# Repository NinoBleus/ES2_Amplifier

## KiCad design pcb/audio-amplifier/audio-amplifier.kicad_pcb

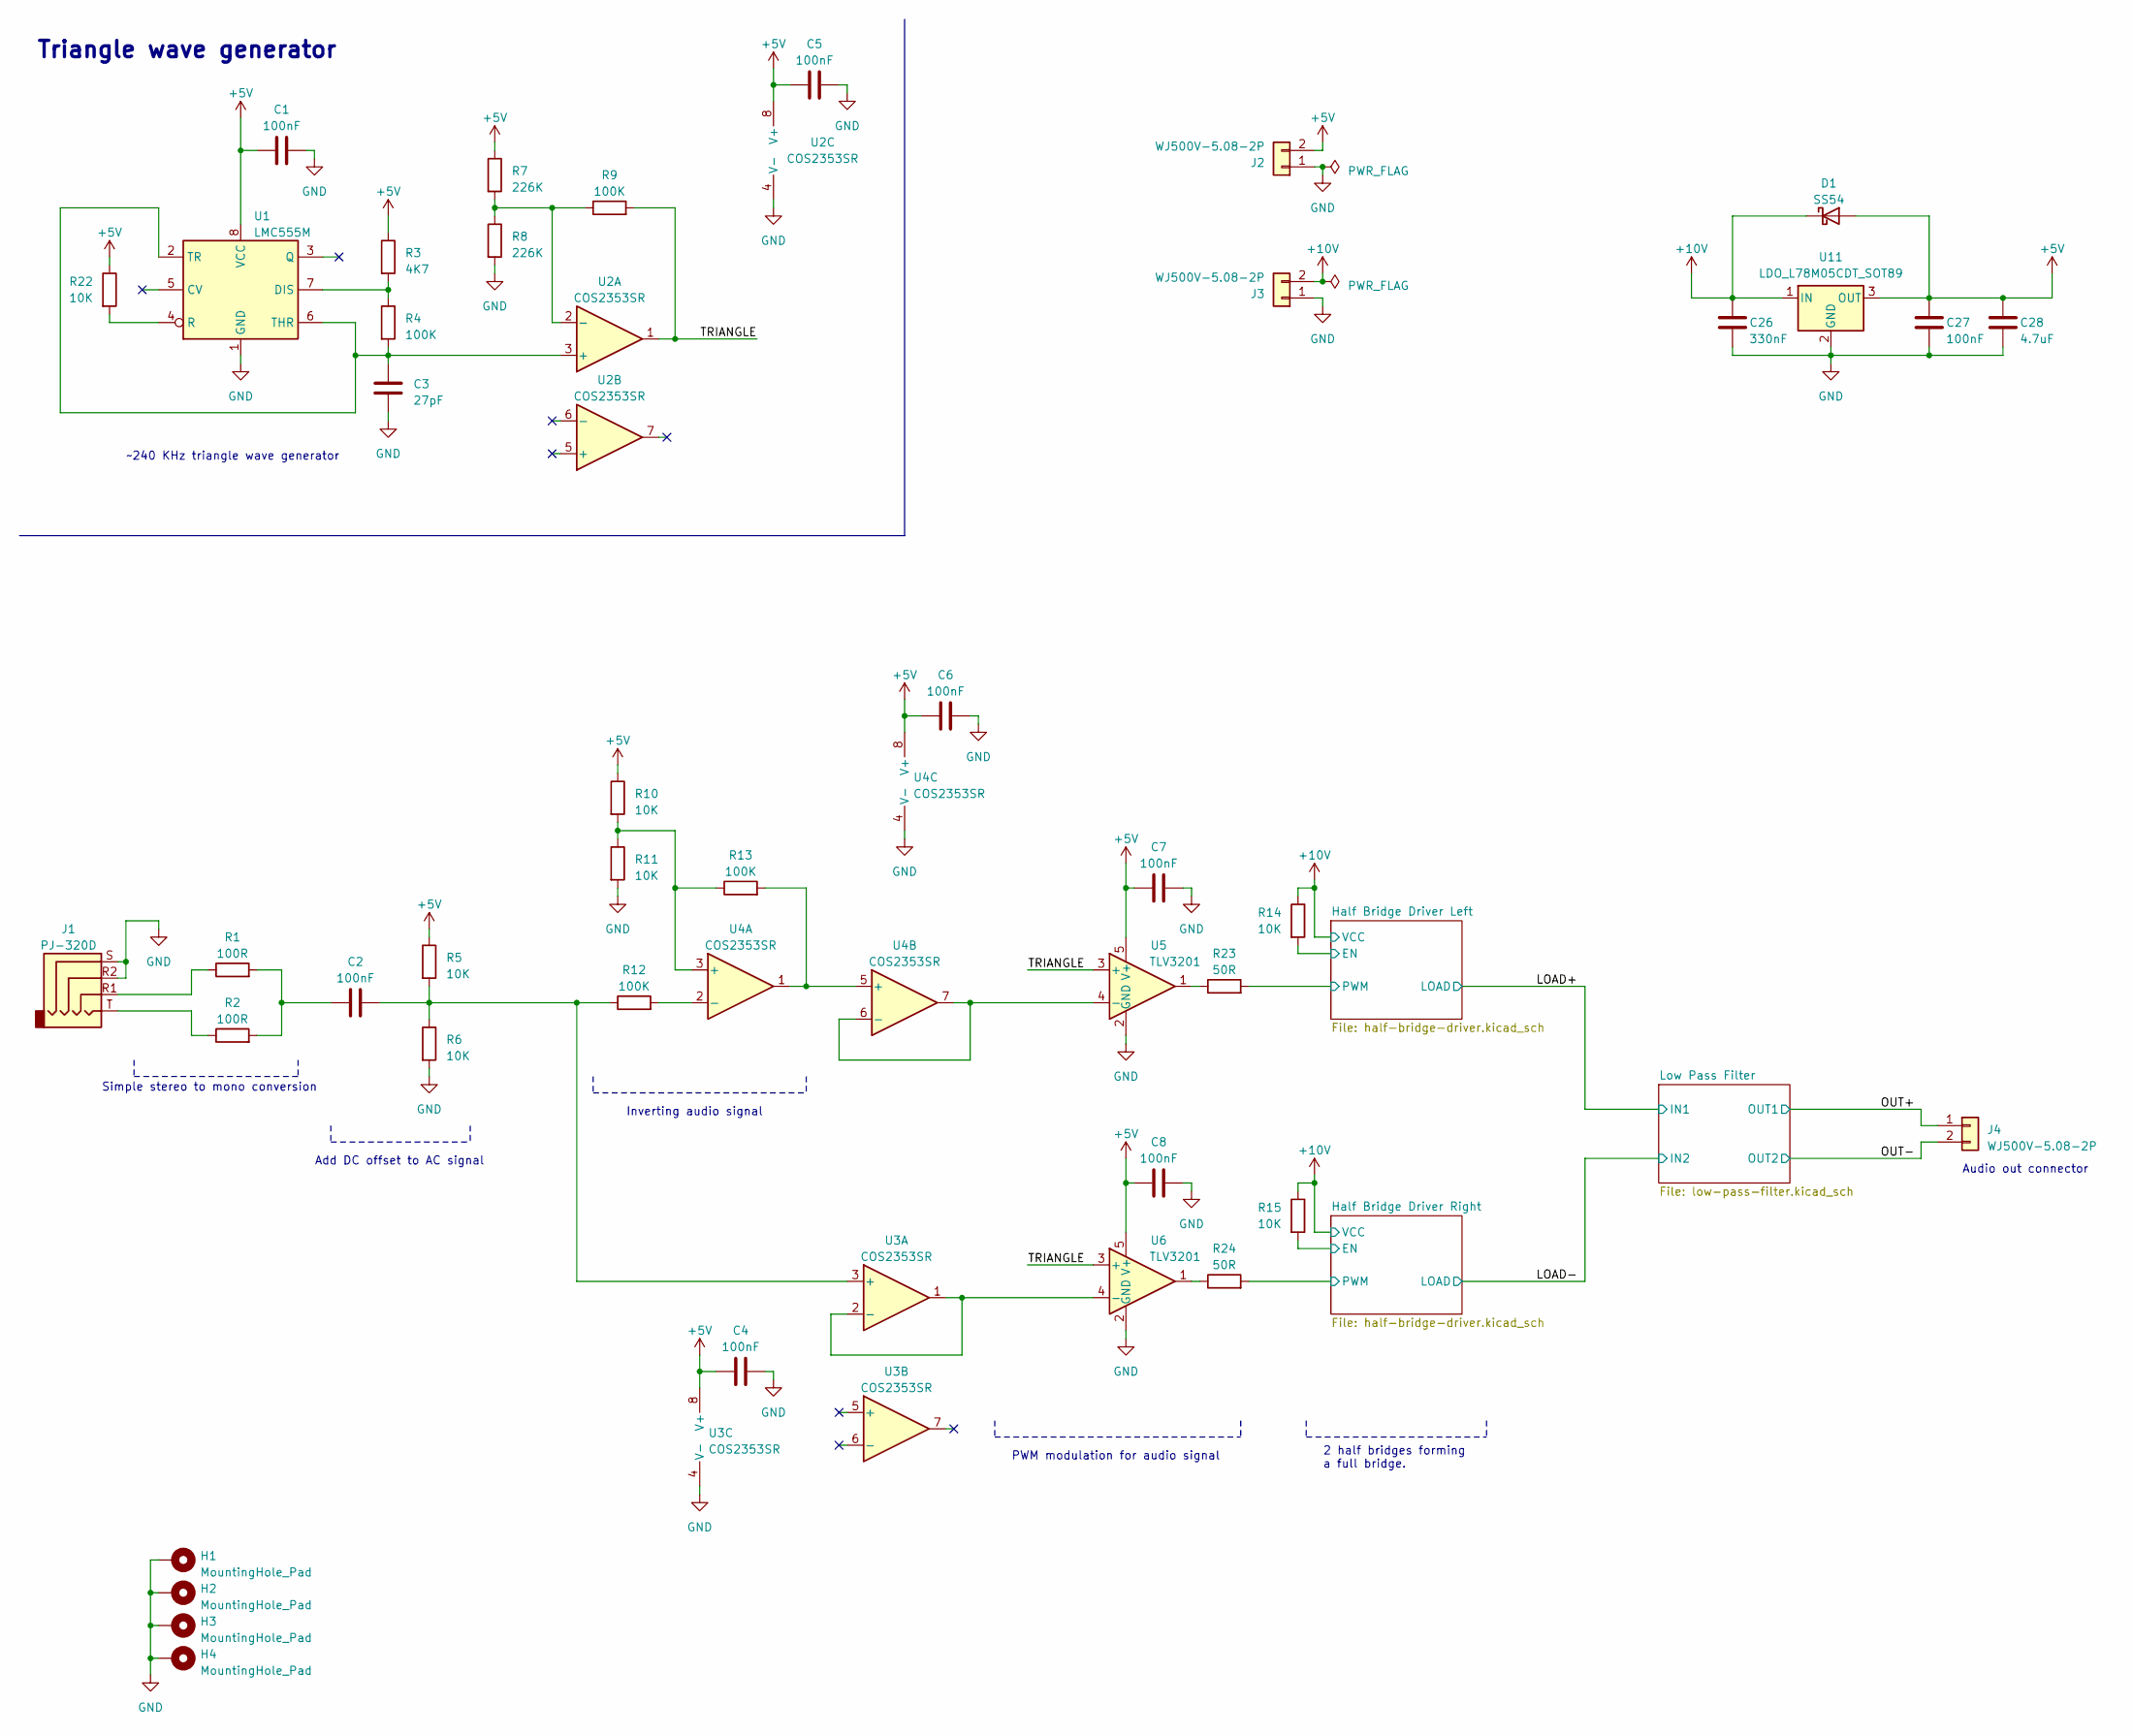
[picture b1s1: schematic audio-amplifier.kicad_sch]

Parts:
C1, C2, C4, C5, C6, C7, C8, C27: 100nF; C_0805_2012Metric; MPN CC0805KRX7R9BB104; LCSC Part # C49678
C3: 27pF; C_0603_1608Metric; MPN GRM1885C1H270FA01D; LCSC Part # C162215
C26: 330nF; C_0805_2012Metric; MPN 0805B334K500NT; LCSC Part # C1740
C28: 4.7uF; C_1206_3216Metric; MPN 1206B475K500NT; LCSC Part # C29823
D1: SS54; D_SMA_Handsoldering; MPN SS54; LCSC Part # C22452
H1, H2, H3, H4: MountingHole_Pad; MountingHole_3.2mm_M3_Pad_Via
J1: PJ-320D; Jack_3.5mm_PJ320D_Horizontal; LCSC Part # C431535
J2, J3, J4: WJ500V-5.08-2P; TerminalBlock_bornier-2_P5.08mm; MPN WJ500V-5.08-2P; LCSC Part # C8465
R1, R2: 100R; R_0805_2012Metric; LCSC Part # C17408
R3: 4K7; R_0603_1608Metric; MPN ARG03BTC4701; LCSC Part # C309085
R4: 100K; R_0603_1608Metric; MPN ARG03BTC1003; LCSC Part # C335088
R5, R6, R10, R11, R14, R15, R22: 10K; R_0805_2012Metric; MPN 0805W8F1002T5E; LCSC Part # C17414
R7, R8: 226K; R_0805_2012Metric; MPN RT0805BRD07226KL; LCSC Part # C865308
R9, R12, R13: 100K; R_0805_2012Metric; MPN 0805W8F1003T5E; LCSC Part # C149504
R23, R24: 50R; R_0805_2012Metric; MPN ARG05FTC0500; LCSC Part # C2828866
U1: LMC555M; SOP-8_3.9x4.9mm_P1.27mm; LCSC Part # C356725
U2, U3, U4: COS2353SR; SOP-8_3.9x4.9mm_P1.27mm; LCSC Part # C2685365
U5, U6: TLV3201; SOT-23-5; LCSC Part # C105188
U11: LDO_L78M05CDT_SOT89; TO-252-2; MPN L78M05CDT; LCSC Part # C55509

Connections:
+5V: C1.1, C4.1, C5.1, C6.1, C7.1, C8.1, C27.1, C28.1, D1.2 (A), J2.2, R3.1, R5.1, R7.1, R10.1, R22.1, U1.8 (VCC), U2.8 (V+), U3.8 (V+), U4.8 (V+), U5.5 (V+), U6.5 (V+), U11.3 (OUT); also elsewhere on the board
+10V: C26.1, D1.1 (K), J3.2, R14.1, R15.1, U11.1 (IN); also elsewhere on the board
/Half Bridge Driver Left/EN: R14.2; also elsewhere on the board
/Half Bridge Driver Left/PWM: R23.2; also elsewhere on the board
/Half Bridge Driver Right/EN: R15.2; also elsewhere on the board
/Half Bridge Driver Right/PWM: R24.2; also elsewhere on the board
/OUT+: J4.1; also elsewhere on the board
/OUT-: J4.2; also elsewhere on the board
/TRIANGLE: R9.2, U2.1, U5.3 (+), U6.3 (+)
GND: C1.2, C3.2, C4.2, C5.2, C6.2, C7.2, C8.2, C26.2, C27.2, C28.2, H1.1, H2.1, H3.1, H4.1, J1.R2, J1.S, J2.1, J3.1, R6.2, R8.2, R11.2, U1.1 (GND), U2.4 (V-), U3.4 (V-), U4.4 (V-), U5.2 (GND), U6.2 (GND), U11.2 (GND); also elsewhere on the board
unnamed: C2.1, R1.2, R2.2
unnamed: J1.R1, R1.1
unnamed: J1.T, R2.1
unnamed: R23.1, U5.1
unnamed: R24.1, U6.1
unnamed: R3.2, R4.1, U1.7 (DIS)
unnamed: R22.2, U1.4 (R)
unnamed: C3.1, R4.2, U1.2 (TR), U1.6 (THR), U2.3 (+)
unnamed: R7.2, R8.1, R9.1, U2.2 (-)
unnamed: C2.2, R5.2, R6.1, R12.1, U3.3 (+)
unnamed: U3.1, U3.2 (-), U6.4 (-)
unnamed: R10.2, R11.1, R13.1, U4.3 (+)
unnamed: R12.2, U4.2 (-)
unnamed: R13.2, U4.1, U4.5 (+)
unnamed: U4.6 (-), U4.7, U5.4 (-)

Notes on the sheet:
Audio out connector
Simple stereo to mono conversion
PWM modulation for audio signal
~240 KHz triangle wave generator
Inverting audio signal
Add DC offset to AC signal
2 half bridges forming a full bridge.
Triangle wave generator

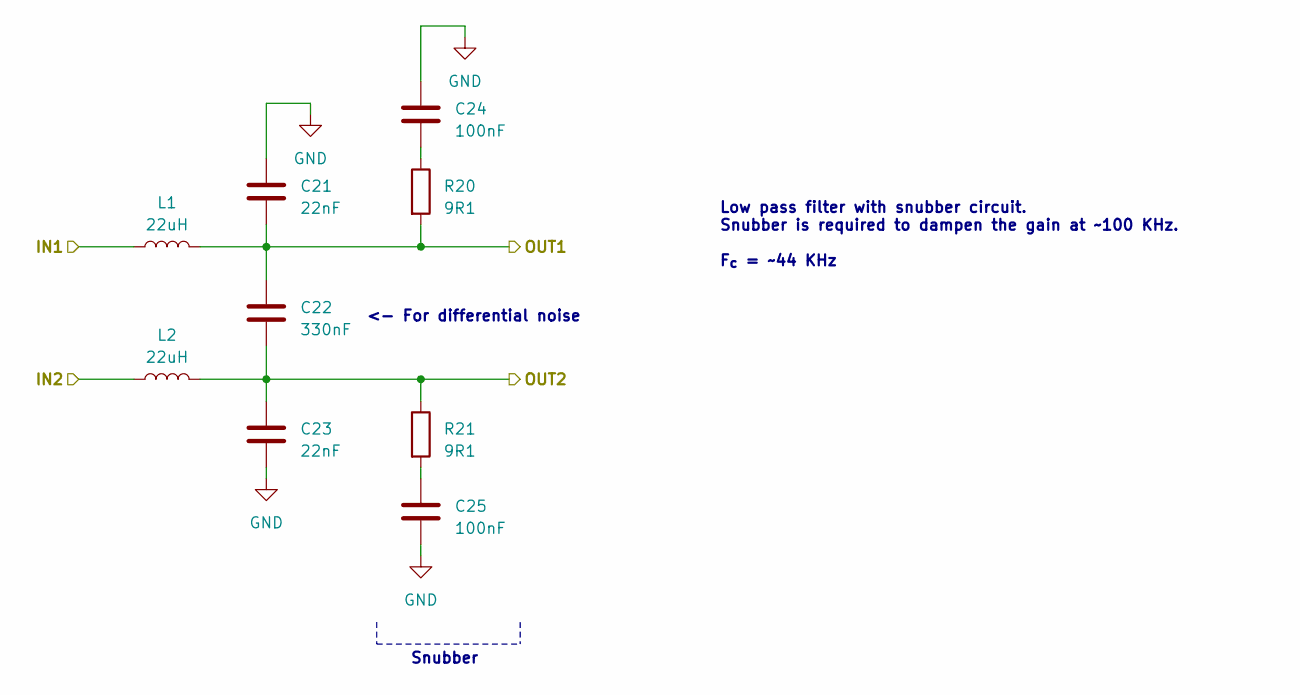
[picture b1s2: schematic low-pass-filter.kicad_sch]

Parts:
C21, C23: 22nF; C_0805_2012Metric; MPN CL21B223KBANNNC; LCSC Part # C1729
C22: 330nF; C_0805_2012Metric; MPN 0805B334K500NT; LCSC Part # C1740
C24, C25: 100nF; C_0805_2012Metric; MPN CC0805KRX7R9BB104; LCSC Part # C49678
L1, L2: 22uH; L_Sunlord_SWPA6045S; MPN SWPA6045S220MT; LCSC Part # C83454
R20, R21: 9R1; R_0805_2012Metric; MPN FRC0805F9R10TS; LCSC Part # C2933515

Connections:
/LOAD+: L1.1; also elsewhere on the board
/LOAD-: L2.1; also elsewhere on the board
/OUT+: C21.2, C22.1, L1.2, R20.2; also elsewhere on the board
/OUT-: C22.2, C23.1, L2.2, R21.1; also elsewhere on the board
GND: C21.1, C23.2, C24.1, C25.2; also elsewhere on the board
unnamed: C24.2, R20.1
unnamed: C25.1, R21.2

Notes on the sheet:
<- For differential noise
Low pass filter with snubber circuit. Snubber is required to dampen the gain at ~100 KHz. F_{c} = ~44 KHz
Snubber

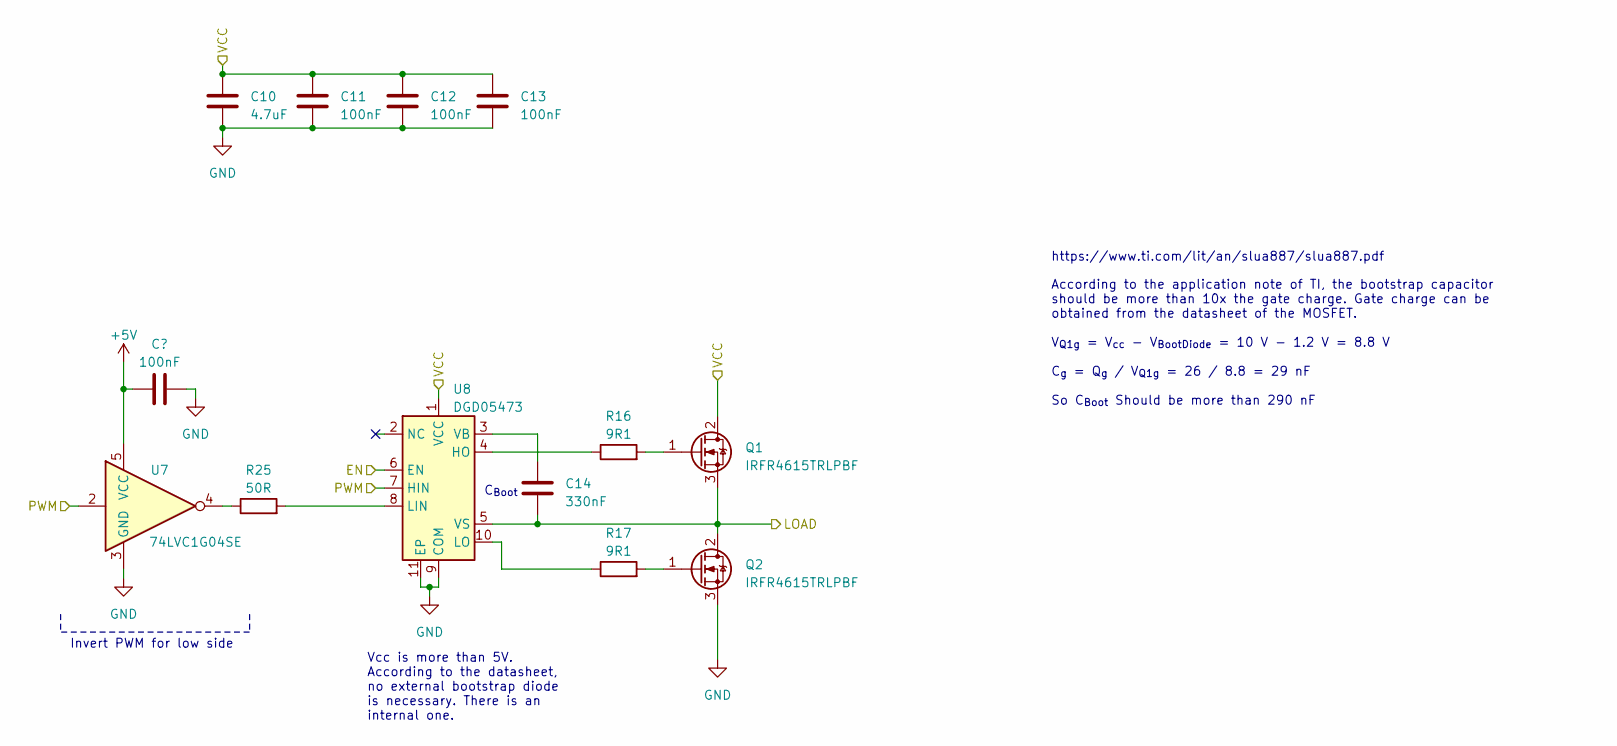
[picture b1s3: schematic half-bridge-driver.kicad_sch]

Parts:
C9, C11, C12, C13: 100nF; C_0805_2012Metric; MPN CC0805KRX7R9BB104; LCSC Part # C49678
C10: 4.7uF; C_1206_3216Metric; MPN 1206B475K500NT; LCSC Part # C29823
C14: 330nF; C_0805_2012Metric; MPN 0805B334K500NT; LCSC Part # C1740
Q1, Q2: IRFR4615TRLPBF; TO-252-2; MPN IRFR4615TRLPBF; LCSC Part # C148159
R16, R17: 9R1; R_0805_2012Metric; MPN FRC0805F9R10TS; LCSC Part # C2933515
R25: 50R; R_0805_2012Metric; MPN ARG05FTC0500; LCSC Part # C2828866
U7: 74LVC1G04SE; SOT-353_SC-70-5; MPN 74LVC1G04SE; LCSC Part # C264081
U8: DGD05473; DFN-10-1EP_3x3mm_P0.5mm_EP1.65x2.38mm; LCSC Part # C189752

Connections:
+5V: C9.1, U7.5 (VCC); also elsewhere on the board
+10V: C10.1, C11.1, C12.1, C13.1, Q1.2 (D), U8.1 (VCC); also elsewhere on the board
/Half Bridge Driver Left/EN: U8.6 (EN); also elsewhere on the board
/Half Bridge Driver Left/PWM: U7.2, U8.7 (HIN); also elsewhere on the board
/LOAD+: C14.2, Q1.3 (S), Q2.2 (D), U8.5 (VS); also elsewhere on the board
GND: C9.2, C10.2, C11.2, C12.2, C13.2, Q2.3 (S), U7.3 (GND), U8.9 (COM), U8.11 (EP); also elsewhere on the board
unnamed: Q1.1 (G), R16.2
unnamed: Q2.1 (G), R17.2
unnamed: R25.1, U7.4
unnamed: R16.1, U8.4 (HO)
unnamed: R25.2, U8.8 (LIN)
unnamed: R17.1, U8.10 (LO)
unnamed: C14.1, U8.3 (VB)

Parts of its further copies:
C15, C17, C18, C19: 100nF; C_0805_2012Metric; MPN CC0805KRX7R9BB104; LCSC Part # C49678
C16: 4.7uF; C_1206_3216Metric; MPN 1206B475K500NT; LCSC Part # C29823
C20: 330nF; C_0805_2012Metric; MPN 0805B334K500NT; LCSC Part # C1740
Q3, Q4: IRFR4615TRLPBF; TO-252-2; MPN IRFR4615TRLPBF; LCSC Part # C148159
R18, R19: 9R1; R_0805_2012Metric; MPN FRC0805F9R10TS; LCSC Part # C2933515
R26: 50R; R_0805_2012Metric; MPN ARG05FTC0500; LCSC Part # C2828866
U9: 74LVC1G04SE; SOT-353_SC-70-5; MPN 74LVC1G04SE; LCSC Part # C264081
U10: DGD05473; DFN-10-1EP_3x3mm_P0.5mm_EP1.65x2.38mm; LCSC Part # C189752

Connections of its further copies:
+5V: C15.1, U9.5 (VCC); also elsewhere on the board
+10V: C16.1, C17.1, C18.1, C19.1, Q3.2 (D), U10.1 (VCC); also elsewhere on the board
/Half Bridge Driver Right/EN: U10.6 (EN); also elsewhere on the board
/Half Bridge Driver Right/PWM: U9.2, U10.7 (HIN); also elsewhere on the board
/LOAD-: C20.2, Q3.3 (S), Q4.2 (D), U10.5 (VS); also elsewhere on the board
GND: C15.2, C16.2, C17.2, C18.2, C19.2, Q4.3 (S), U9.3 (GND), U10.9 (COM), U10.11 (EP); also elsewhere on the board
unnamed: Q3.1 (G), R18.2
unnamed: Q4.1 (G), R19.2
unnamed: R26.1, U9.4
unnamed: R18.1, U10.4 (HO)
unnamed: R26.2, U10.8 (LIN)
unnamed: R19.1, U10.10 (LO)
unnamed: C20.1, U10.3 (VB)

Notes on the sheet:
C_{Boot}
Vcc is more than 5V. According to the datasheet, no external bootstrap diode is necessary. There is an internal one.
https://www.ti.com/lit/an/slua887/slua887.pdf
Invert PWM for low side
According to the application note of TI, the bootstrap capacitor should be more than 10x the gate charge. Gate charge can be obtained from the datasheet of the MOSFET. V_{Q1g} = V_{cc} - V_{BootDiode} = 10 V - 1.2 V = 8.8 V C_{g} = Q_{g} / V_{Q1g} = 26 / 8.8 = 29 nF So C_{Boot} Should be more than 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

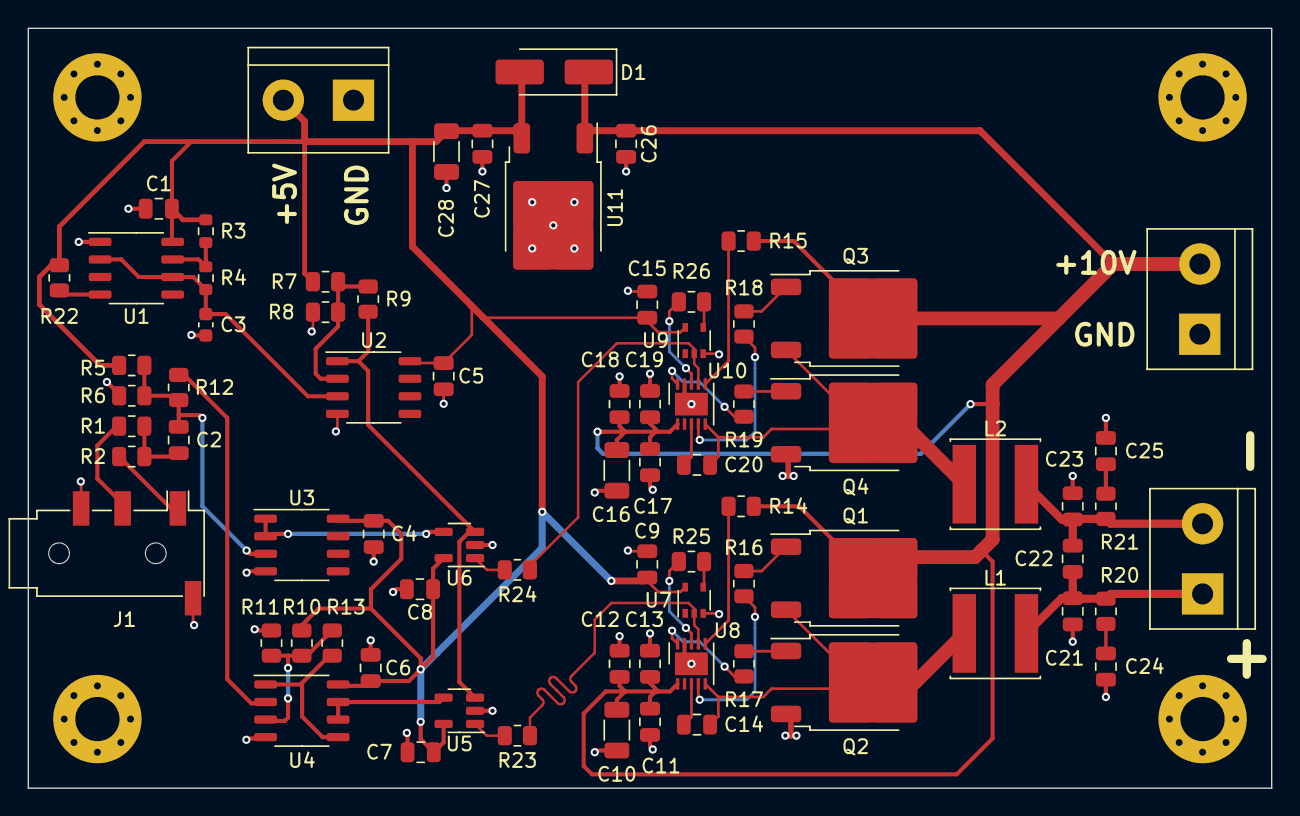
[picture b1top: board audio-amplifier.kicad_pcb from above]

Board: 4 copper layers, 90.0 x 55.0 mm, 80 parts (0 on the bottom side), 43 nets.

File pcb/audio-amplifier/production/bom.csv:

Designator,Footprint,Quantity,Value,LCSC Part #
"C1, C11, C12, C13, C15, C17, C18, C19, C2, C24, C25, C27, C4, C5, C6, C7, C8, C9",0805,18,100nF,C49678
"C10, C16, C28",1206,3,4.7uF,C29823
"C14, C20, C22, C26",0805,4,330nF,C1740
"C21, C23",0805,2,22nF,C1729
C3,0603,1,27pF,C162215
D1,D_SMA_Handsoldering,1,SS54,C22452
"H1, H2, H3, H4",MountingHole_3.2mm_M3_Pad_Via,4,MountingHole_Pad,
J1,Jack_3.5mm_PJ320D_Horizontal,1,PJ-320D,C431535
"J2, J3, J4",TerminalBlock_bornier-2_P5.08mm,3,WJ500V-5.08-2P,C8465
"L1, L2",L_Sunlord_SWPA6045S,2,22uH,C83454
"Q1, Q2, Q3, Q4",TO-252-2,4,IRFR4615TRLPBF,C148159
"R1, R2",0805,2,100R,C17408
"R10, R11, R14, R15, R22, R5, R6",0805,7,10K,C17414
"R12, R13, R9",0805,3,100K,C149504
"R16, R17, R18, R19, R20, R21",0805,6,9R1,C2933515
"R23, R24, R25, R26",0805,4,50R,C2828866
R3,0603,1,4K7,C309085
R4,0603,1,100K,C335088
"R7, R8",0805,2,226K,C865308
U1,SOP-8_3.9x4.9mm_P1.27mm,1,LMC555M,C356725
"U10, U8",DFN-10-1EP_3x3mm_P0.5mm_EP1.65x2.38mm,2,DGD05473,C189752
U11,TO-252-2,1,LDO_L78M05CDT_SOT89,C55509
"U2, U3, U4",SOP-8_3.9x4.9mm_P1.27mm,3,COS2353SR,C2685365
"U5, U6",SOT-23-5,2,TLV3201,C105188
"U7, U9",SOT-353_SC-70-5,2,74LVC1G04SE,C264081

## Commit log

2023-02-28 Aanmaken altium files
2023-02-28 Add gitignore
2023-03-09 Add gitignore for LTspice
2023-03-09 sims: Add current LTspice simulations
2023-03-22 pcb: Remove Altium project
2023-03-22 pcb: Init kicad project
2023-03-24 sims: Add SPICE models
2023-03-24 sims: Add simulations
2023-03-24 pcb: Add PCB
2023-03-24 pcb: Comment out .csv in gitignore
2023-04-18 Update sim
2023-04-18 Add old PCB
2023-04-18 Add updated PCB
2023-04-18 Update ibom
2023-04-18 Fix via placement
